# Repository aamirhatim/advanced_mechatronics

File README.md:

# ME 433: Advanced Mechatronics
#### Aamir Husain
#### Spring 2018

This repo contains all mini-projects completed in ME 433: Advanced Mechatronics at Northwestern University.

### [HW 1](hw1): PIC32 Setup
### [HW 2](hw2): Schematic Design
### [HW 3](hw3): PCB Design
### [HW 4](hw4): SPI Communication with a DAC
### [HW 5](hw5): I2C Communication with a Pin Expander
### [HW 6](hw6): Controlling an LCD Display
### [HW 7](hw7): Reading an IMU with I2C
### [HW 8](hw8): Coding with MPLAB Harmony
### [HW 9](hw9): USB Communication
### [HW 10](hw10): Digital Signal Processing
### [HW 11](hw11): Tilt-Sensitive Computer Mouse
### [HW 12](hw12): Intro to Android App Development
### [HW 13](hw13): Accessing the Android Camera
### [HW 14](hw14): Android - PIC Communication
### [HW 15](hw15): CAD 3D Printing, and Laser Cutting
### [HW 16](hw16): PI Motor Control
### [HW 17](hw17): Path Detection
### [HW 18](hw18): Putting Everything Together - A Line Following Robot

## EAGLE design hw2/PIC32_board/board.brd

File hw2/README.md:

# Homework 2
The schematic for the circuit built in Homework 1 was made in Eagle. Custom parts were made for a few of the components.
The zip gerber files can be found [here](PIC32_board/gerber.zip).

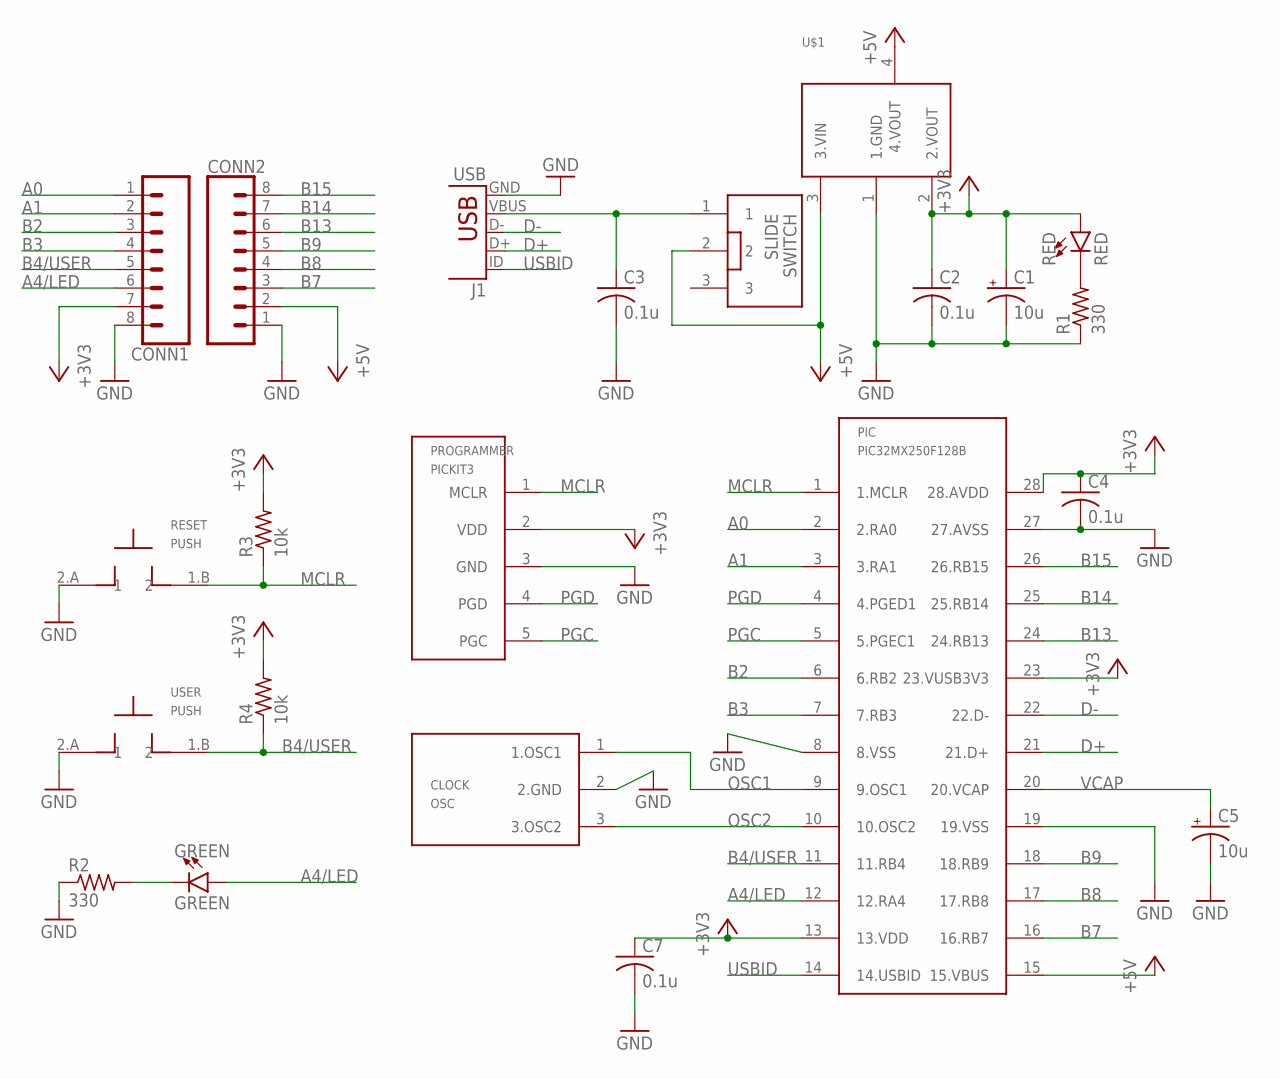
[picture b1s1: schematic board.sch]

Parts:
C1, C5: 10u; CAP-POL-0603
C2, C3, C4, C7: 0.1u; C0603
CLOCK: OSC; NU32V7_RESONATOR-SMD
CONN1, CONN2: CONN_08"; 1X08
GREEN: GREEN; LED-0603
J1: USB; NU32V7_USB-MINIB
PIC: PIC32MX250F128B; DIL28-3
PROGRAMMER: PICKIT3; 1X05
R1, R2: 330; R0603
R3, R4: 10k; R0603
RED: RED; LED-0603
RESET: PUSH; NU32V7_MOM_SW
SWITCH: SLIDE
U$1: SOT-223; NU32V7_SOT223
USER: PUSH; NU32V7_MOM_SW

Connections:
+3V3: C1.1 (+), C2.1, C4.1, C7.1, CONN1.7, PIC.13 (13.VDD), PIC.23 (23.VUSB3V3), PIC.28 (28.AVDD), PROGRAMMER.2 (VDD), R3.2, R4.2, RED.A, U$1.2 (2.VOUT)
+5V: CONN2.2, PIC.15 (15.VBUS), SWITCH.2, U$1.3 (3.VIN), U$1.4 (4.VOUT)
A0: CONN1.1, PIC.2 (2.RA0)
A1: CONN1.2, PIC.3 (3.RA1)
A4/LED: CONN1.6, GREEN.A, PIC.12 (12.RA4)
B2: CONN1.3, PIC.6 (6.RB2)
B3: CONN1.4, PIC.7 (7.RB3)
B4/USER: CONN1.5, PIC.11 (11.RB4), R4.1, USER.1.B (2)
B7: CONN2.3, PIC.16 (16.RB7)
B8: CONN2.4, PIC.17 (17.RB8)
B9: CONN2.5, PIC.18 (18.RB9)
B13: CONN2.6, PIC.24 (24.RB13)
B14: CONN2.7, PIC.25 (25.RB14)
B15: CONN2.8, PIC.26 (26.RB15)
D+: J1.D+, PIC.21 (21.D+)
D-: J1.D-, PIC.22 (22.D-)
GND: C1.2 (-), C2.2, C3.2, C4.2, C5.2 (-), C7.2, CLOCK.2 (2.GND), CONN1.8, CONN2.1, J1.GND, PIC.8 (8.VSS), PIC.19 (19.VSS), PIC.27 (27.AVSS), PROGRAMMER.3 (GND), R1.1, R2.1, RESET.2.A (1), U$1.1 (1.GND), USER.2.A (1)
MCLR: PIC.1 (1.MCLR), PROGRAMMER.1 (MCLR), R3.1, RESET.1.B (2)
unnamed: GREEN.C, R2.2
unnamed: R1.2, RED.C
unnamed: C3.1, J1.VBUS, SWITCH.1
OSC1: CLOCK.1 (1.OSC1), PIC.9 (9.OSC1)
OSC2: CLOCK.3 (3.OSC2), PIC.10 (10.OSC2)
PGC: PIC.5 (5.PGEC1), PROGRAMMER.5 (PGC)
PGD: PIC.4 (4.PGED1), PROGRAMMER.4 (PGD)
USBID: J1.ID, PIC.14 (14.USBID)
VCAP: C5.1 (+), PIC.20 (20.VCAP)

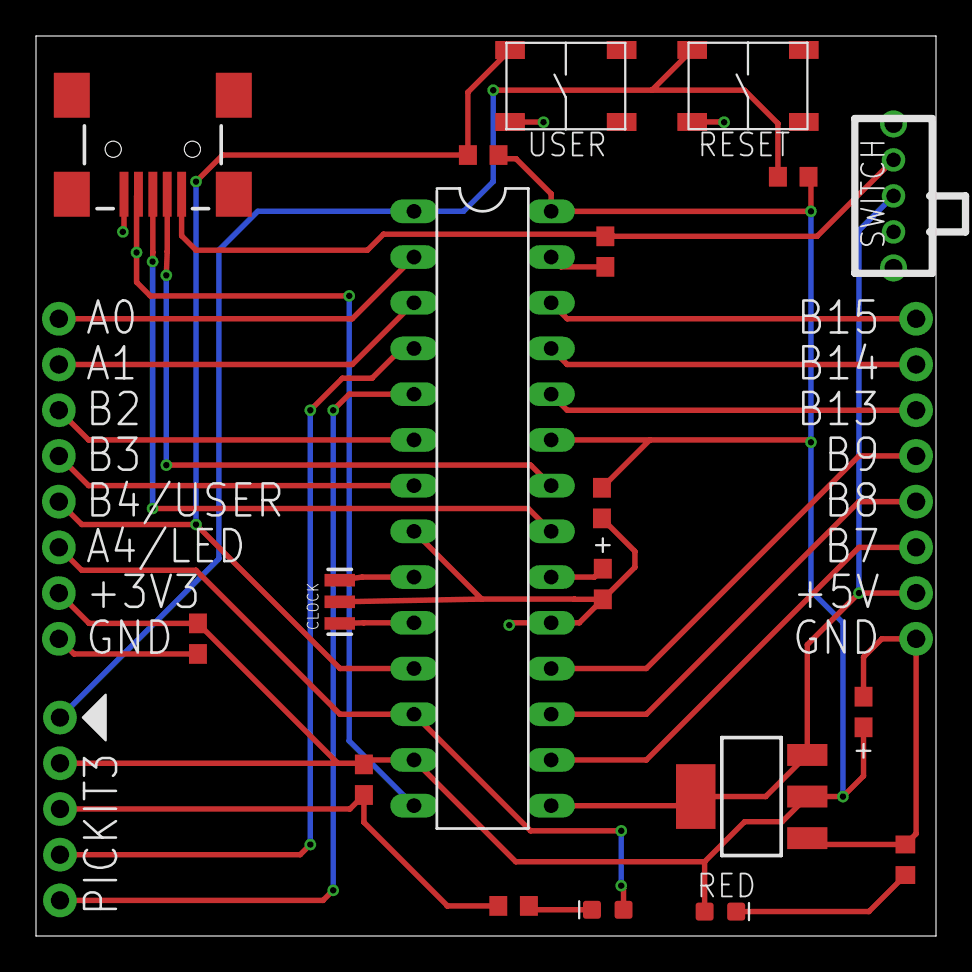
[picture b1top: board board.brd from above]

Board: 2 copper layers, 50.0 x 50.0 mm, 22 parts (0 on the bottom side), 27 nets.

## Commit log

2018-04-09 Add voltage regulator scope images
2018-04-09 Add circuit board
2018-04-09 Add empty project
2018-04-09 Add circuit diagram image
2018-04-10 Rename project, add pragma values to main.c
2018-04-10 turn on LED
2018-04-10 Add push button config
2018-04-10 Blink LED at 1000Hz
2018-04-10 Add code to turn off LED while button is pushed
2018-04-10 Clean up code
2018-04-10 Add new diagram and breadboard pictures
2018-04-10 Add README
2018-04-10 Eit image syntax
2018-04-10 Wrong image extension
2018-04-10 Move README to hw1 folder
2018-04-10 Add over all README
2018-04-10 Edit hw1 README
2018-04-10 Edit link to code in hw1 README
2018-04-11 Fix typo
2018-04-11 Start Eagle schematic and library
2018-04-12 Add completed schematic and library
2018-04-12 Add README and schematic diagram
2018-04-12 Remove .#* files from git
2018-04-12 Do not track .spf files
2018-04-12 Add PCB layout
2018-04-15 Complete board design, add PCB gerber files.
2018-04-15 Add PCB images and update README
2018-04-15 Add link to gerber zip
2018-04-15 Move clock further from PIC
2018-04-17 Move gerber zip to hw3
2018-04-17 Remove line in README
2018-04-19 Set SPI pins for PIC
2018-04-20 Change which pins to use for DAC elements
2018-04-21 Add spi communication files
2018-04-21 Testing out SPI communication
2018-04-21 SPI communication successful
2018-04-21 Create function for writing data to DAC
2018-04-21 Sin wave working
2018-04-21 Triangle function working
2018-04-22 Add screenshot
2018-04-22 Add to readme
2018-04-22 Add DAC schematic and image
2018-04-22 Edit pin label
2018-04-22 Add hw5 folder and README
2018-04-22 Add expander chip to schematic library
2018-04-22 Begin coding for hw5
2018-04-22 Add I2C set and get functions
2018-04-23 Add value for I2C2TRN
2018-04-23 Test communication with expander
2018-04-24 Add PIC LED control
2018-04-24 Add LED toggle function
2018-04-24 Toggle i2c light with pic light
2018-04-24 button functionanlity working properly
2018-04-24 Remove toggle function
2018-04-24 Add circuit diagram
2018-04-24 Edit schematic labels
2018-04-24 Add folder for HW 6
2018-04-24 Add LCD to library
2018-04-24 Add initial code for LCD
2018-04-24 Able to print to LCD
2018-04-24 Clear leftover characters from previous iteration
2018-04-24 Draw outline of progress bar
2018-04-24 Percent loading bar working properly
2018-04-24 Add FPS counter
2018-04-25 Add boundary checker before printing pixel
2018-04-25 Increment counter at 10Hz
2018-04-27 Communication with IMU established
2018-04-27 Turn on gyro and accelerometer
2018-04-28 Multiple read working
2018-04-28 Combine byes to get IMU info
2018-04-28 Add LCD library
2018-04-28 LCD display communication working
2018-04-29 Print x and y acceleration to LCD
2018-04-29 Draw axes
2018-04-29 Acceleration prints to screen
2018-04-29 Add tilt bars
2018-04-29 Make bars thicker
2018-05-01 Change to read at 20Hz
2018-05-01 Add IMU schematic and README info
2018-05-01 Add to main README
2018-05-01 Add HW 8
2018-05-01 HW 1 replicated
2018-05-01 Replicate HW 7
2018-05-08 USB communication working
2018-05-08 Add info to READMEs
2018-05-08 Communicate with IMU
2018-05-10 Read at 5hz, send data at 100hz
2018-05-10 Only send data when hitting 'r'
2018-05-10 Initial HW 10 commit
2018-05-10 Add hw10 link to main README
2018-05-10 Replicate HW 9
2018-05-10 Add MATLAB function
2018-05-10 Add filters.c, function to initialize a buffer for MAF
2018-05-10 Implement MAF
2018-05-11 Add FIR and IIR filters
2018-05-11 Plot graphs
2018-05-11 Edit typo
2018-05-11 Fix link
2018-05-11 Add figure labels
2018-05-13 Sample mouse code working
2018-05-13 Diagonal movementworking
2018-05-13 Slow down movement
2018-05-13 Read from IMU and scale values for mouse movement
2018-05-13 Mouse movement working with IMU signal
2018-05-13 Adjust scaling for good speed
2018-05-14 Add mouse click feature to USER button
2018-05-14 Trying to edit button press delay
2018-05-14 Add README info
2018-05-14 Add filter graphs
2018-05-14 Edit README
2018-05-22 Update gerber files for processing
2018-05-23 First commit for android app
2018-05-23 Change app name
2018-05-23 Change app text
2018-05-23 Add linear layout
2018-05-23 Add seek bar and more text
2018-05-23 Add slider bar functionality and display its change
2018-05-23 Add screenshot and readme info
2018-05-23 Add permissions to app for camera
2018-05-23 Prevent app from rotating
2018-05-23 Get cameras working
2018-05-25 Add slider
2018-05-25 Make slider change threshhold value
2018-05-25 Put color detector in a larger for loop to scan whole image
2018-05-25 Reduce number of lines drawn for speed
2018-05-25 display threshold value
2018-05-25 Add info to README
2018-05-25 Add HW 14 and set up code
2018-05-31 Add hw14
2018-05-31 Add hw 15
2018-05-31 Add images
2018-06-01 PIC-Computer communication working
2018-06-01 Add copycat app for hw 15, add root for Greens app
2018-06-01 add button and another text view
2018-06-01 Add scroll view
2018-06-01 initialize new widget objects
2018-06-01 slider and button functionality working
2018-06-01 Numbers from PIC sent to scrollview
2018-06-01 send button value to PIC
2018-06-01 Reorganize file location
2018-06-01 Add README description
2018-06-10 Updates to Greens
2018-06-10 Add line finder app
2018-06-10 Look for black or blackish pixels
2018-06-10 Create moving average filter for pixels
2018-06-10 Look for left side of track
2018-06-10 Detect and edge
2018-06-10 Detect left and right edges
2018-06-12 Add functions for edge detection. Clean up and comment code
2018-06-12 Add project info
2018-06-12 Add links to main README
2018-06-13 Add README for hw16
2018-06-13 Add CDC setup code
2018-06-13 CDC setup complete
2018-06-13 Copy code from hw14
2018-06-13 Add motor controller setup
2018-06-13 Working on Pi control code
2018-06-14 PI controller working
2018-06-14 Edit master README
2018-06-14 Add link to interrupt
2018-06-14 Add final project PIC code
2018-06-15 Add initial ndroid code and copy PIc code from hw16
2018-06-15 Add USB communication for app
2018-06-15 Update final tweaks for speed and tuning.
2018-06-15 Move final app to hw18 folder
2018-06-15 Add pics to README
